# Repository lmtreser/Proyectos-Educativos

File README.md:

# Proyectos Educativos

Proyectos educativos (de diversos origenes) relacionados con trabajos prácticos de las escuelas EEST N°2, EEST N°3 y EEST N°5 de la ciudad de Mar del Plata.

Los diagramas esquemáticos en su mayoría están realizados con Autodesk EAGLE (v7 o superior), y en algunos casos con KiCad (v7 o superior). Mientras que el código generalmente está basado en la API de Arduino.

La ultima versión se puede descargar desde el repositorio [en este enlace](https://github.com/lmtreser/Proyectos).

## Contenidos

- `Analogicas 44` Trabajos "Aplicaciones de Electrónica Analógica I"
- `ArduProfe` Placa entrenadora para Arduino Nano, por el prof. Alejandro Cordero
- `Difusión` Charlas, eventos y difusiones en general
- `Diseño Asistido` Trabajos de diseño de esquemas y PCBs
- `Eduqube` PocketQube educative kit, by [Innova Space](https://www.innova-space.com)
- `Entrenadora Digital` Trabajo práctico "Aplicaciones de Electrónica Digital III"
- `Internet of Things` Trabajos relacionados al IoT
- `Lenguajes Electrónicos` Trabajos "Lenguajes Electrónicos II"
- `Micro Automata` Trabajo práctico "Montaje de Proyectos Electrónicos III"
- `Pulsador de Potencia` Feria de Ciencias, trabajo interdisciplinar, extracurricular
- `Robotec` Competencia de Robótica intercolegial, trabajo interdisciplinar, extracurricular
- `Sensor de Proximidad` Trabajo práctico "Montaje de Proyectos Electrónicos III"

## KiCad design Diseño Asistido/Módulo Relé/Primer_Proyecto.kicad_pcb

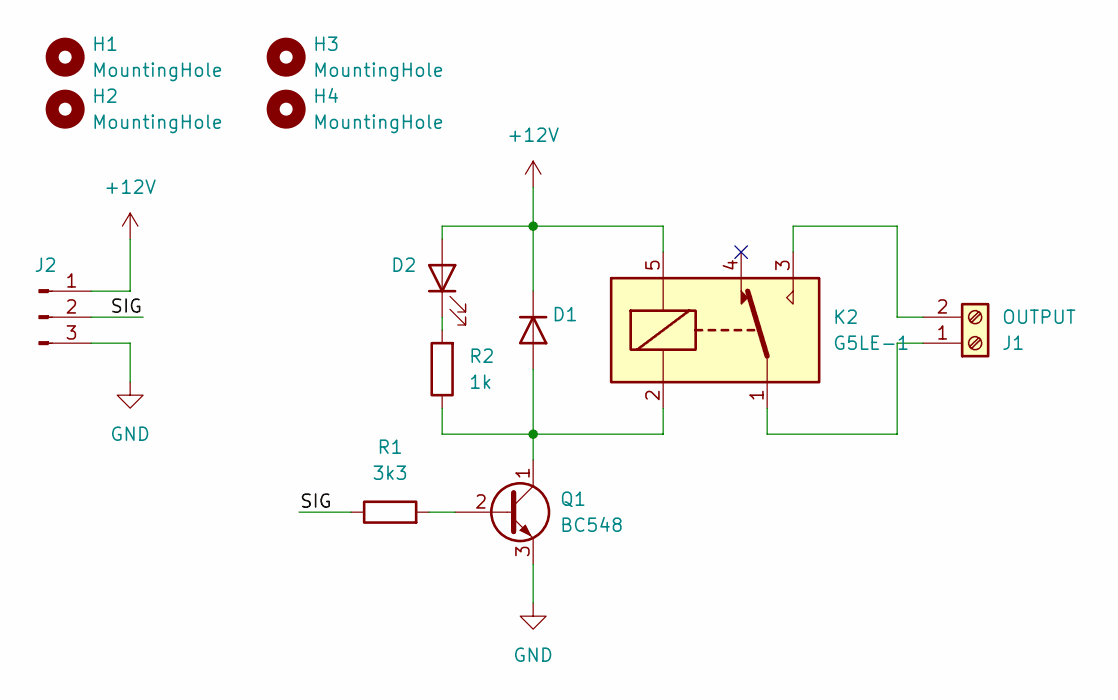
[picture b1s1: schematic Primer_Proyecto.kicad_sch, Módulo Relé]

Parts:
D1: 1N4007; D_DO-41_SOD81_P10.16mm_Horizontal
D2: LED; LED_D3.0mm
H1, H2, H3, H4: MountingHole; MountingHole_3.2mm_M3
J1: OUTPUT; TerminalBlock_MetzConnect_Type011_RT05502HBWC_1x02_P5.00mm_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
J2: Conn_01x03_Pin; PinHeader_1x03_P1.27mm_Vertical
K2: G5LE-1; Relay_SPDT_Omron-G5LE-1
Q1: BC548; TO-92_Inline
R1: 3k3; R_Axial_DIN0207_L6.3mm_D2.5mm_P7.62mm_Horizontal
R2: 1k; R_Axial_DIN0207_L6.3mm_D2.5mm_P7.62mm_Horizontal

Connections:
+12V: D1.1 (K), D2.2 (A), J2.1, K2.5
/SIG: J2.2, R1.1
GND: J2.3, Q1.3 (E)
unnamed: D1.2 (A), K2.2, Q1.1 (C), R2.1
unnamed: D2.1 (K), R2.2
unnamed: J1.1, K2.1
unnamed: J1.2, K2.3
unnamed: Q1.2 (B), R1.2

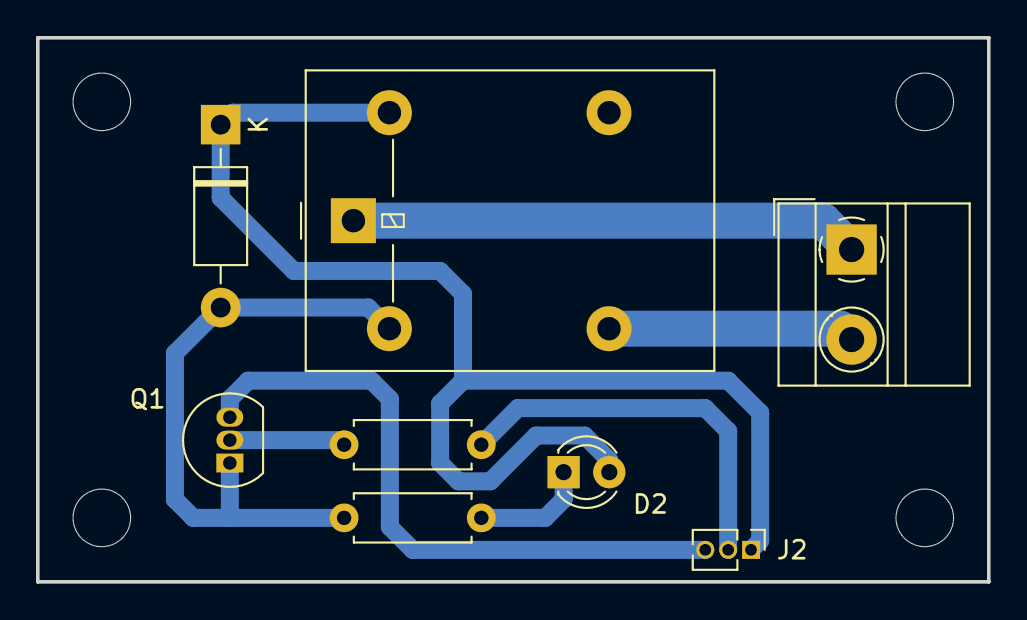
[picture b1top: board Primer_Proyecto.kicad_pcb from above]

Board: 2 copper layers, 52.8 x 30.2 mm, 12 parts (0 on the bottom side), 8 nets.

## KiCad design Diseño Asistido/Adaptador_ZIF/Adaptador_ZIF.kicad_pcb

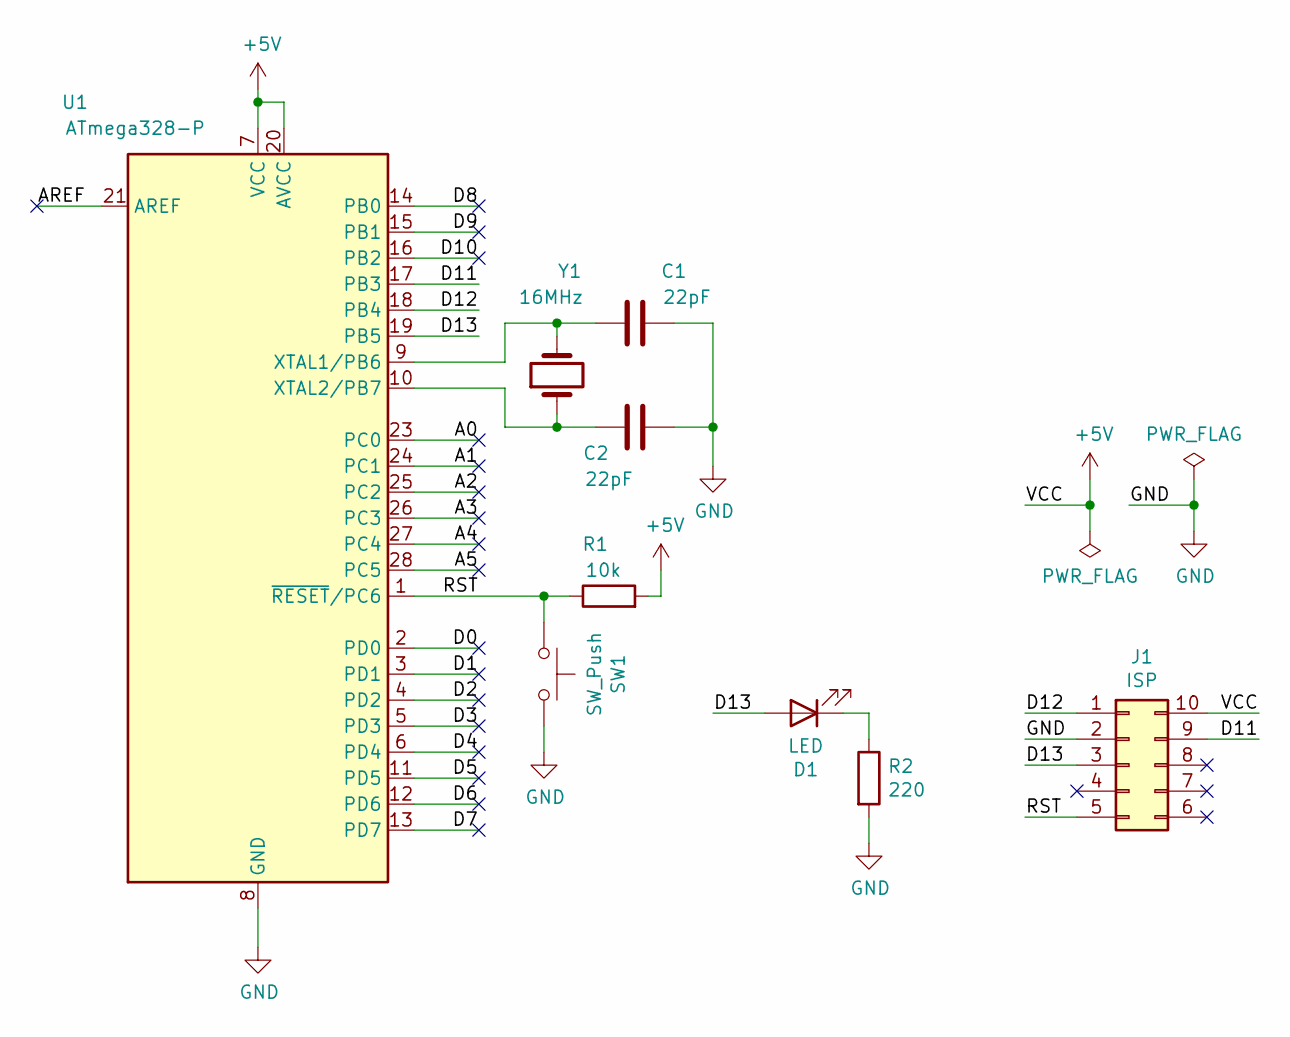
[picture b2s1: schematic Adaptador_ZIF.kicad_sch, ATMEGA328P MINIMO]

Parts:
C1, C2: 22pF; C_Disc_D5.0mm_W2.5mm_P2.50mm
D1: LED; LED_D3.0mm
J1: ISP; IDC-Header_2x05_P2.54mm_Vertical
R1: 10k; R_Axial_DIN0207_L6.3mm_D2.5mm_P10.16mm_Horizontal
R2: 220; R_Axial_DIN0207_L6.3mm_D2.5mm_P10.16mm_Horizontal
SW1: SW_Push; SW_PUSH_6mm_H5mm
U1: ATmega328-P; DIP_Socket-28_W6.9_W7.62_W10.16_W12.7_W13.5_3M_228-4817-00-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
Y1: 16MHz; Crystal_HC49-4H_Vertical

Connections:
+5V: J1.10, R1.2, U1.7 (VCC), U1.20 (AVCC)
/A0: U1.23 (PC0)
/A1: U1.24 (PC1)
/A2: U1.25 (PC2)
/A3: U1.26 (PC3)
/A4: U1.27 (PC4)
/A5: U1.28 (PC5)
/AREF: U1.21 (AREF)
/D0: U1.2 (PD0)
/D1: U1.3 (PD1)
/D2: U1.4 (PD2)
/D3: U1.5 (PD3)
/D4: U1.6 (PD4)
/D5: U1.11 (PD5)
/D6: U1.12 (PD6)
/D7: U1.13 (PD7)
/D8: U1.14 (PB0)
/D9: U1.15 (PB1)
/D10: U1.16 (PB2)
/D11: J1.9, U1.17 (PB3)
/D12: J1.1, U1.18 (PB4)
/D13: D1.2 (A), J1.3, U1.19 (PB5)
/RST: J1.5, R1.1, SW1.1, U1.1 (~RESET/PC6)
GND: C1.1, C2.1, J1.2, R2.2, SW1.2, U1.8 (GND), U1.22 (GND)
unnamed: C1.2, U1.9 (XTAL1/PB6), Y1.2
unnamed: C2.2, U1.10 (XTAL2/PB7), Y1.1
unnamed: D1.1 (K), R2.1

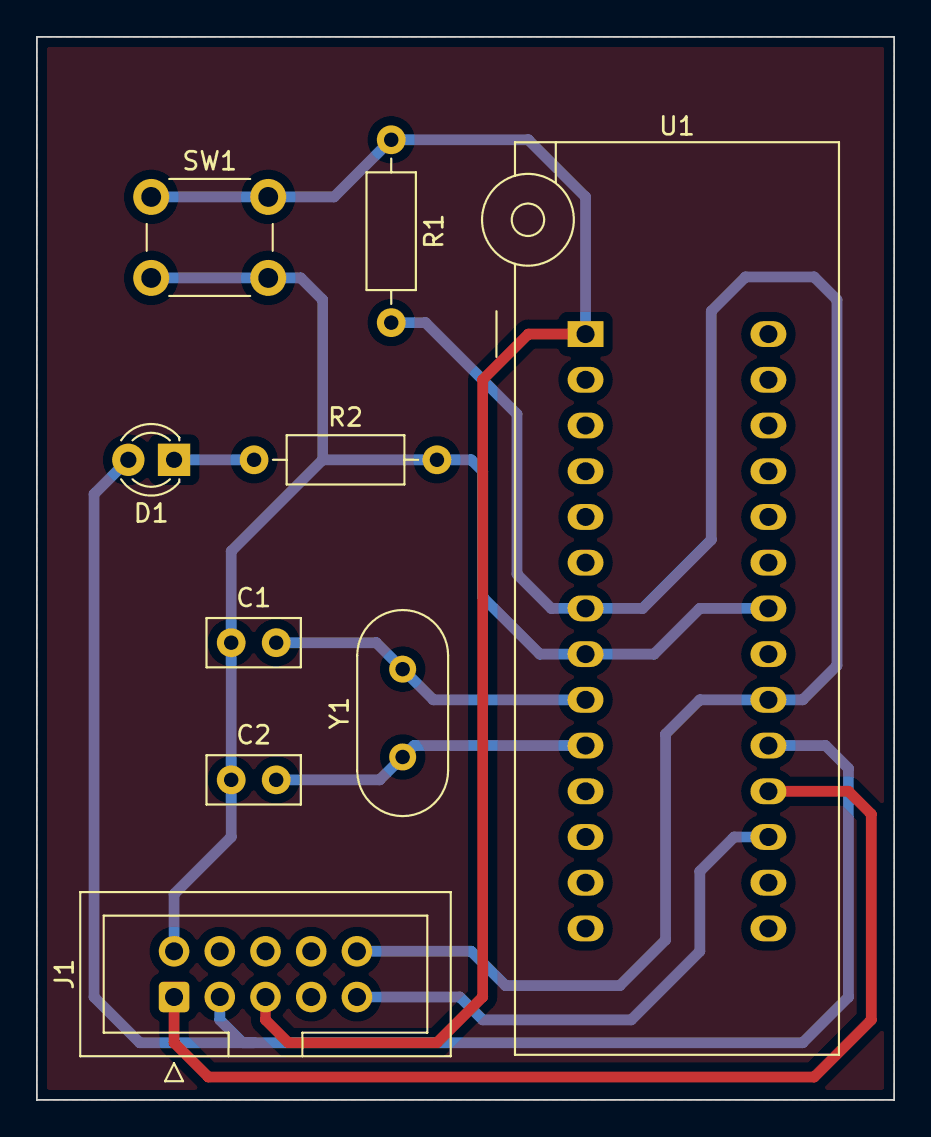
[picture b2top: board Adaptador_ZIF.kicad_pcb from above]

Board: 2 copper layers, 47.6 x 59.1 mm, 9 parts (0 on the bottom side), 9 nets.

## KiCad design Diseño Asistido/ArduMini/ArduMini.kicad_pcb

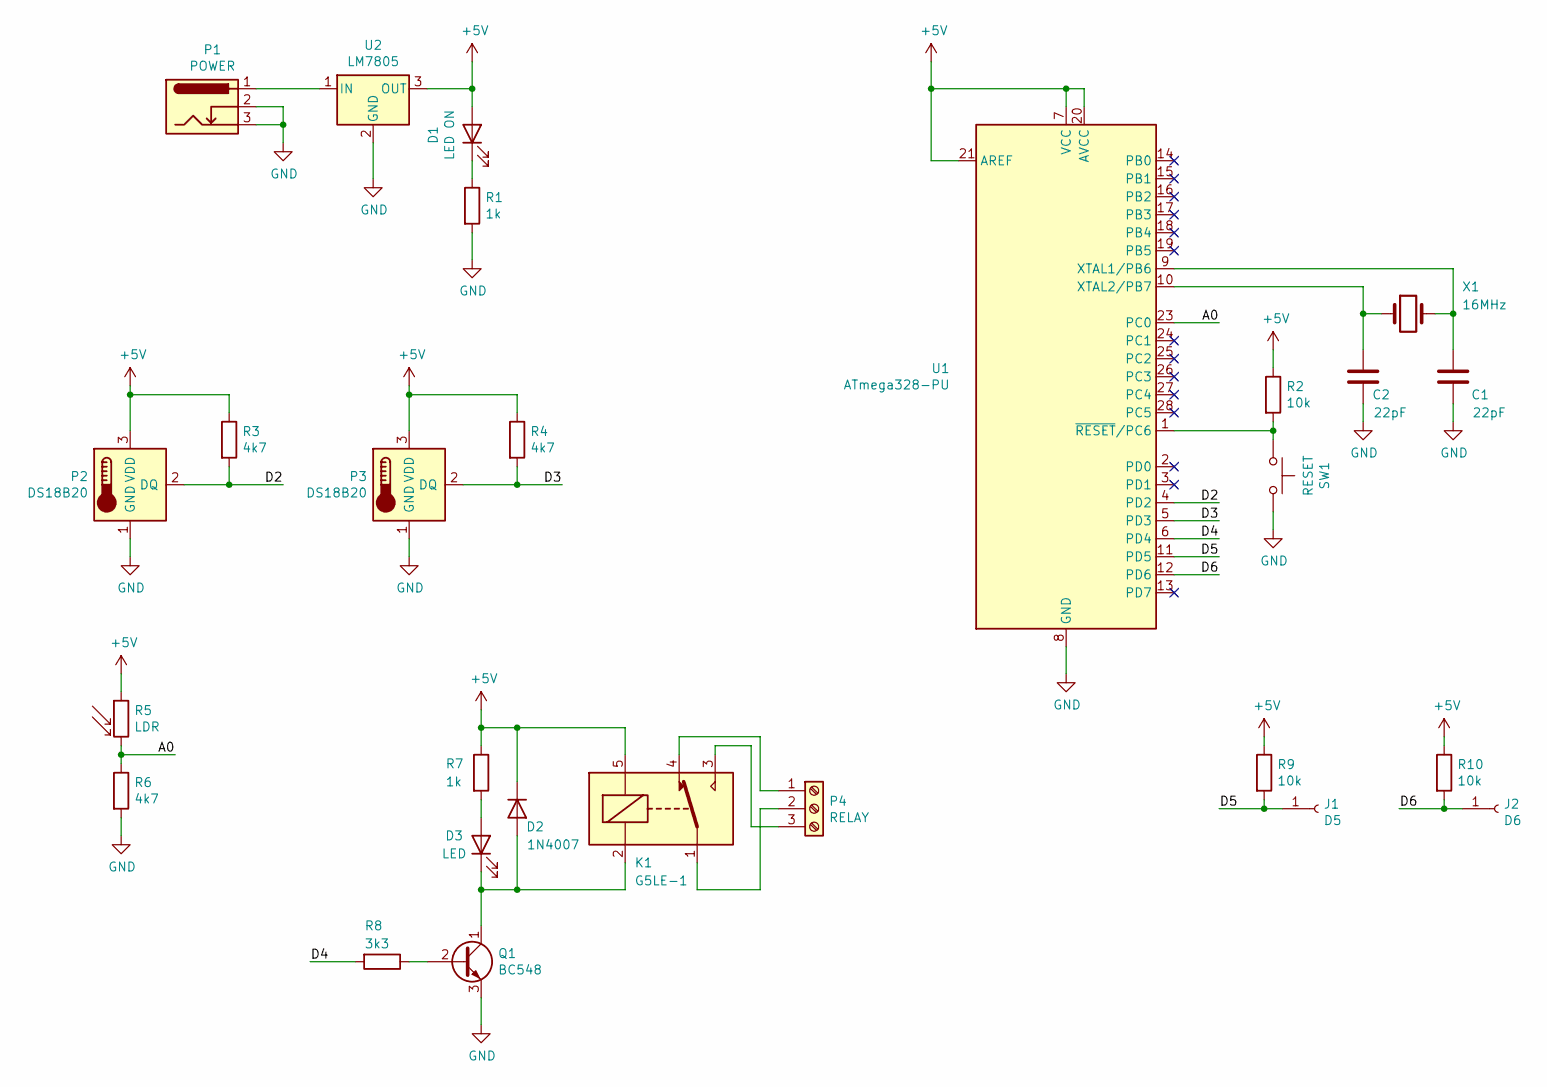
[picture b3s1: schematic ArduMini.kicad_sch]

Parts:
C1, C2: 22pF; C_Disc_D5.0mm_W2.5mm_P2.50mm
D1: LED ON; LED_D5.0mm
D2: 1N4007; D_DO-41_SOD81_P10.16mm_Horizontal
D3: LED; LED_D3.0mm
J1: D5; PinHeader_1x01_P1.00mm_Vertical
J2: D6; PinHeader_1x01_P1.00mm_Vertical
K1: G5LE-1; Relay_SPDT_Omron-G5LE-1
P1: POWER; BarrelJack_Horizontal
P2, P3: DS18B20; TerminalBlock_Altech_AK300-3_P5.00mm
P4: RELAY; TerminalBlock_Altech_AK300-3_P5.00mm
Q1: BC548; TO-92_Inline
R1, R7: 1k; R_Axial_DIN0207_L6.3mm_D2.5mm_P10.16mm_Horizontal
R2, R9, R10: 10k; R_Axial_DIN0207_L6.3mm_D2.5mm_P10.16mm_Horizontal
R3, R4, R6: 4k7; R_Axial_DIN0207_L6.3mm_D2.5mm_P10.16mm_Horizontal
R5: LDR; R_LDR_5.0x4.1mm_P3mm_Vertical
R8: 3k3; R_Axial_DIN0207_L6.3mm_D2.5mm_P10.16mm_Horizontal
SW1: RESET; SW_PUSH_6mm_H5mm
U1: ATmega328-PU; DIP-28_W7.62mm
U2: LM7805; TO-220-3_Vertical
X1: 16MHz; Crystal_HC49-4H_Vertical

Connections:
+5V: D1.2 (A), D2.1 (K), K1.5, P2.3 (VDD), P3.3 (VDD), R2.1, R3.1, R4.1, R5.1, R7.1, R9.1, R10.1, U1.7 (VCC), U1.20 (AVCC), U1.21 (AREF), U2.3 (OUT)
/A0: R5.2, R6.1, U1.23 (PC0)
/D2: P2.2 (DQ), R3.2, U1.4 (PD2)
/D3: P3.2 (DQ), R4.2, U1.5 (PD3)
/D4: R8.2, U1.6 (PD4)
/D5: J1.1, R9.2, U1.11 (PD5)
/D6: J2.1, R10.2, U1.12 (PD6)
GND: C1.1, C2.1, P1.2, P1.3, P2.1 (GND), P3.1 (GND), Q1.3 (E), R1.2, R6.2, SW1.2, U1.8 (GND), U1.22 (GND), U2.2 (GND)
unnamed: C1.2, U1.9 (XTAL1/PB6), X1.2
unnamed: C2.2, U1.10 (XTAL2/PB7), X1.1
unnamed: D1.1 (K), R1.1
unnamed: D2.2 (A), D3.1 (K), K1.2, Q1.1 (C)
unnamed: D3.2 (A), R7.2
unnamed: K1.1, P4.2
unnamed: K1.3, P4.3
unnamed: K1.4, P4.1
unnamed: P1.1, U2.1 (IN)
unnamed: Q1.2 (B), R8.1
unnamed: R2.2, SW1.1, U1.1 (~RESET/PC6)

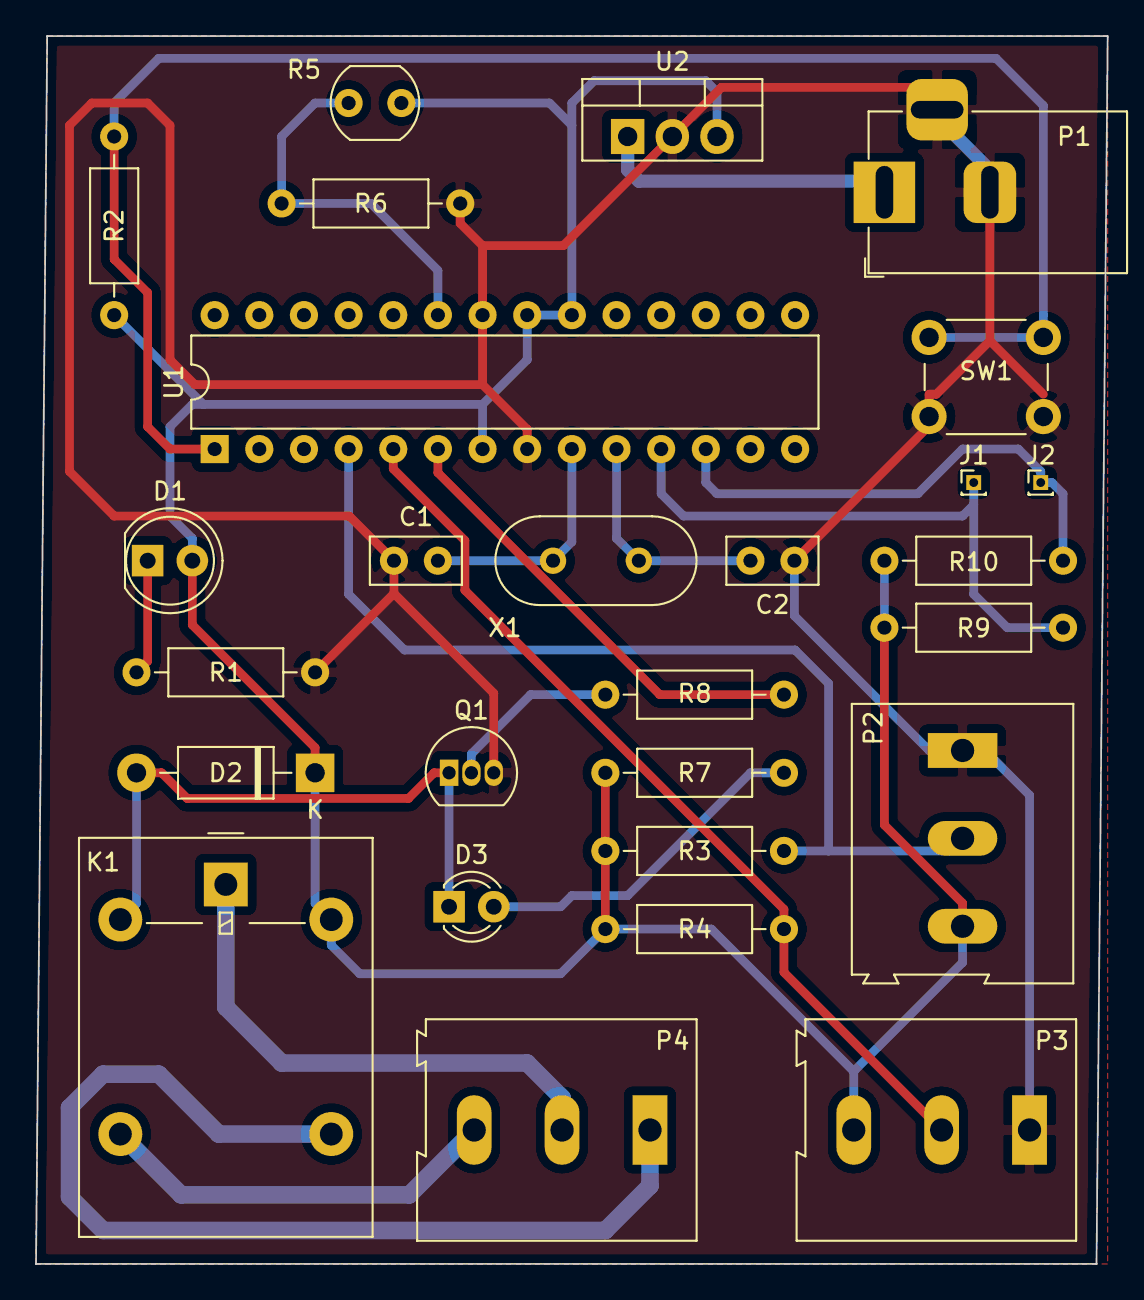
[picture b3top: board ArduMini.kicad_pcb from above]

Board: 2 copper layers, 61.0 x 69.9 mm, 27 parts (0 on the bottom side), 19 nets.

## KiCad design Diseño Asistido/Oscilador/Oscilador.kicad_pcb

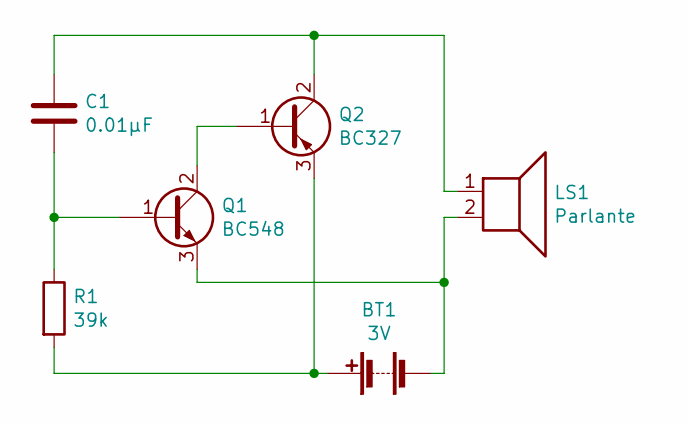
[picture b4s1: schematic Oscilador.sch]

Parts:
BT1: 3V; BatteryHolder_Keystone_2462_2xAA
C1: 0.01µF; C_Disc_D5.0mm_W2.5mm_P2.50mm
LS1: Parlante; TerminalBlock_Altech_AK300-2_P5.00mm
Q1: BC548; TO-92
Q2: BC327; TO-92
R1: 39k; R_Axial_DIN0207_L6.3mm_D2.5mm_P15.24mm_Horizontal

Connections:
unnamed: BT1.1 (+), Q2.3 (E), R1.2
unnamed: BT1.2 (-), LS1.2, Q1.3 (E)
unnamed: C1.1, LS1.1, Q2.2 (C)
unnamed: C1.2, Q1.1 (B), R1.1
unnamed: Q1.2 (C), Q2.1 (B)

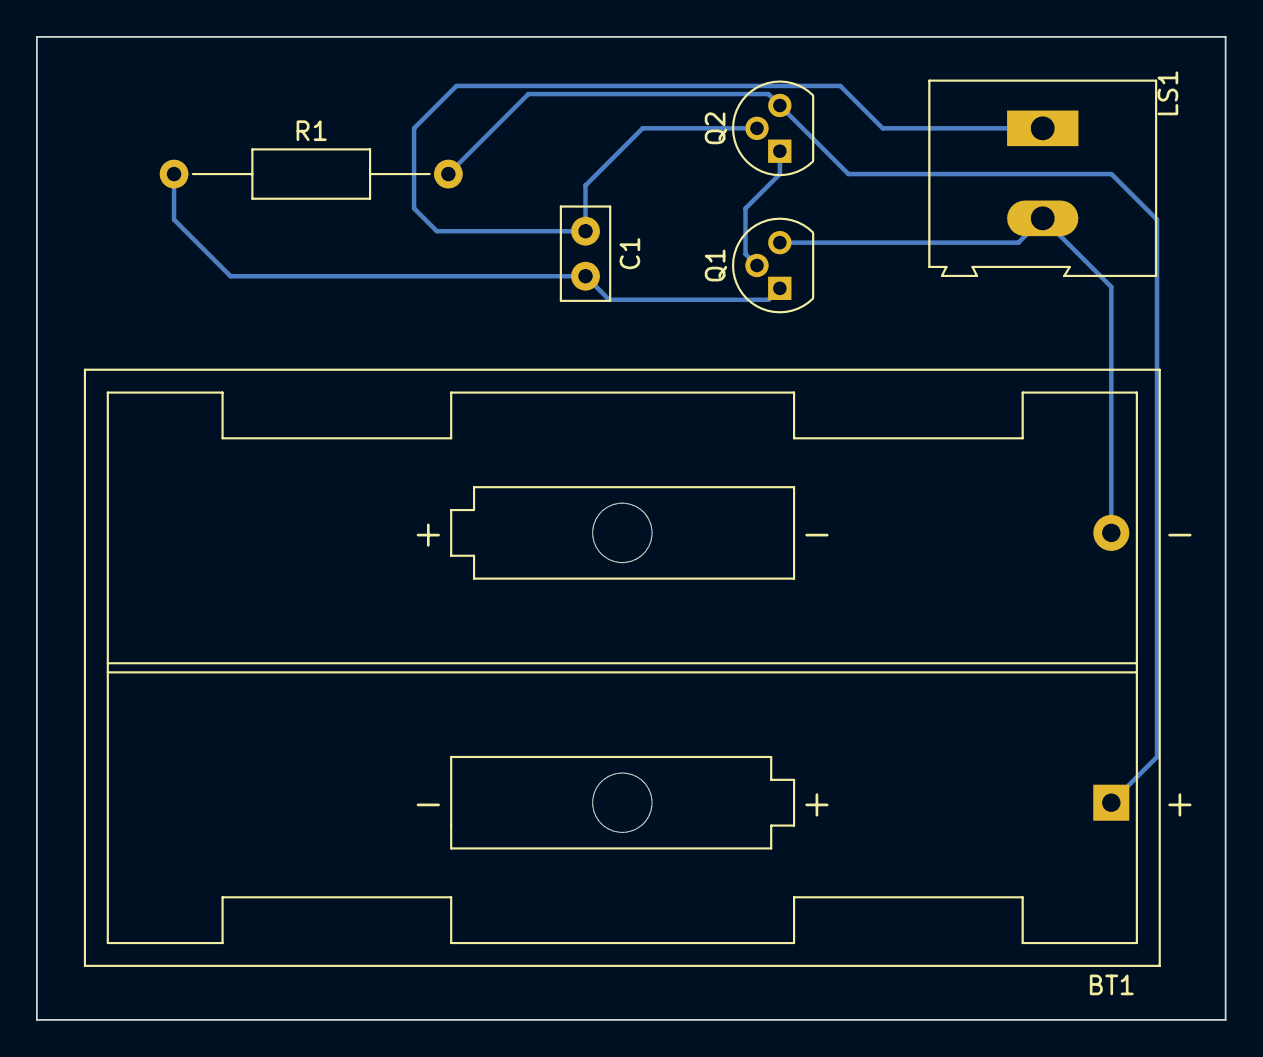
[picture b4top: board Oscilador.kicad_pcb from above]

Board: 2 copper layers, 66.0 x 54.6 mm, 6 parts (0 on the bottom side), 5 nets.

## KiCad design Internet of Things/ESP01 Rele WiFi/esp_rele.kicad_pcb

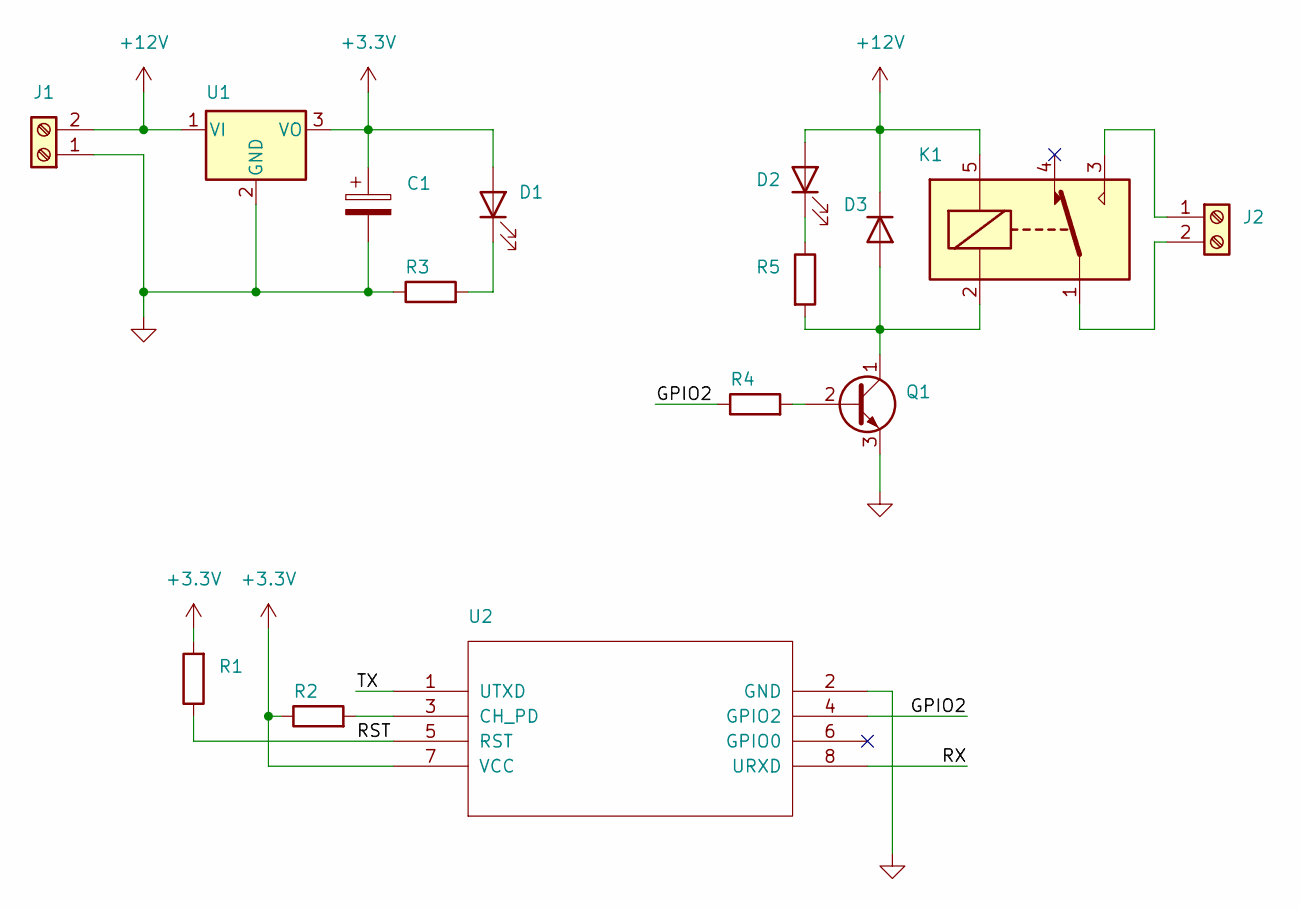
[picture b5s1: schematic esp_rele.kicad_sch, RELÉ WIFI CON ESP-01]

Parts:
C1: 25uF; CP_Radial_D6.3mm_P2.50mm
D1, D2: LED; LED_D3.0mm
D3: 1N4007; D_DO-41_SOD81_P10.16mm_Horizontal
J1, J2: Screw_Terminal_01x02; TerminalBlock_Phoenix_MKDS-1,5-2_1x02_P5.00mm_Horizontal
K1: G5LE-1; Relay_SPDT_Omron-G5LE-1
Q1: BC548; TO-92_Inline
R1, R2, R4: 3k3; R_Axial_DIN0207_L6.3mm_D2.5mm_P7.62mm_Horizontal
R3, R5: 470; R_Axial_DIN0207_L6.3mm_D2.5mm_P7.62mm_Horizontal
U1: AZ1117T; TO-220-3_Vertical
U2: ESP-01v090; ESP-01

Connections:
+3.3V: C1.1, D1.2 (A), R1.2, R2.1, U1.3 (VO), U2.7 (VCC)
+12V: D2.2 (A), D3.1 (K), J1.2, K1.5, U1.1 (VI)
/GPIO2: R4.1, U2.4 (GPIO2)
/RST: R1.1, U2.5 (RST)
/RX: U2.8 (URXD)
/TX: U2.1 (UTXD)
GND: C1.2, J1.1, Q1.3 (E), R3.1, U1.2 (GND), U2.2 (GND)
unnamed: D1.1 (K), R3.2
unnamed: D2.1 (K), R5.1
unnamed: D3.2 (A), K1.2, Q1.1 (C), R5.2
unnamed: J2.1, K1.3
unnamed: J2.2, K1.1
unnamed: Q1.2 (B), R4.2
unnamed: R2.2, U2.3 (CH_PD)

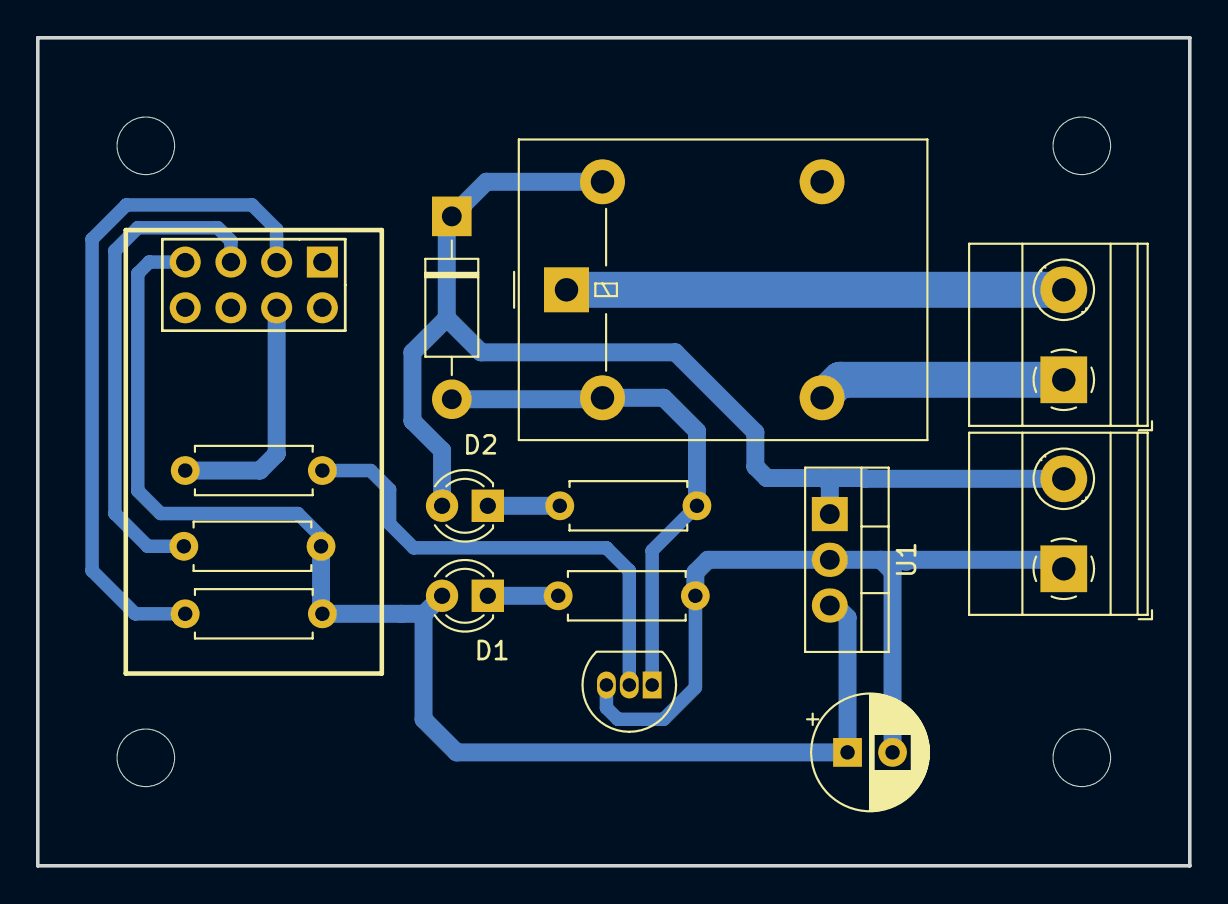
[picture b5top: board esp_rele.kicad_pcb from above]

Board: 2 copper layers, 64.0 x 46.0 mm, 19 parts (0 on the bottom side), 12 nets.

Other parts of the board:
REF01, REF02, REF03, REF04: MountingHole_3.2mm_M3

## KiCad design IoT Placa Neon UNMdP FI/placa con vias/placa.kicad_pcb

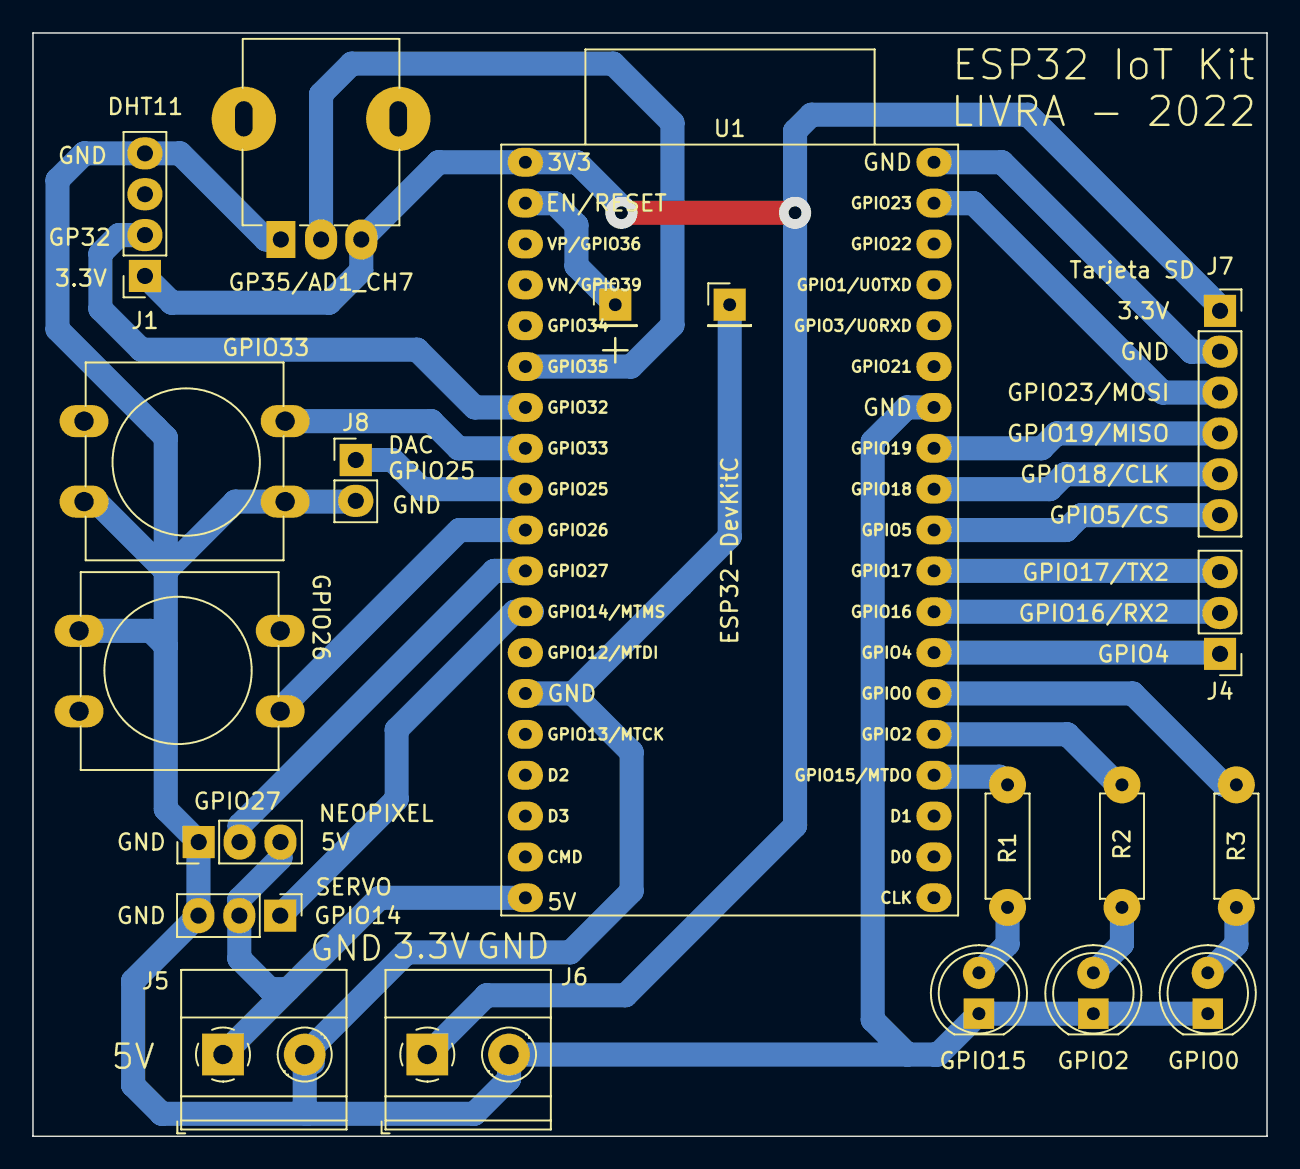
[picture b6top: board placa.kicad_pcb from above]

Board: 2 copper layers, 76.7 x 68.6 mm, 20 parts (0 on the bottom side), 24 nets.

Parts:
D1: ROJO; LED_D5.0mm
D2: AMARILLO; LED_D5.0mm
D3: VERDE; LED_D5.0mm
J1: DHT11; PinSocket_1x04_P2.54mm_Vertical
J2: NeoPixel; PinHeader_1x03_P2.54mm_Vertical
J3: Servo; PinHeader_1x03_P2.54mm_Vertical
J4: Conn_01x03_Male; PinHeader_1x03_P2.54mm_Vertical
J5, J6: Screw_Terminal_01x02; TerminalBlock_Phoenix_MKDS-1,5-2-5.08_1x02_P5.08mm_Horizont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
J7: Conn_01x06_Female; PinSocket_1x06_P2.54mm_Vertical
J8: Conn_01x02_Male; PinHeader_1x02_P2.54mm_Vertical
J11, J12: Conn_01x01_Male; PinHeader_1x01_P2.54mm_Vertical
R1, R2, R3: 470; R_Axial_DIN0207_L6.3mm_D2.5mm_P7.62mm_Horizontal
RV1: R_Potentiometer; Potentiometer_Alpha_RD901F-40-00D_Single_Vertical
SW1, SW2: SW_Push; SW_PUSH-12mm
U1: ESP32-DevKitC

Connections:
3.3v: J1.1, J6.1, J7.1, RV1.3, U1.1 (3V3)
5v: J2.3, J3.2, J5.1, U1.19 (5V)
/EN: J11.1, U1.2 (CHIP_PU)
GND: D1.1 (K), D2.1 (K), D3.1 (K), J1.4, J2.1, J3.3, J5.2, J6.2, J7.2, J8.2, J12.1, RV1.1, SW1.2, SW2.2, U1.14 (GND), U1.32 (GND), U1.38 (GND)
unnamed: D1.2 (A), R3.2
unnamed: D2.2 (A), R2.1
unnamed: D3.2 (A), R1.1
unnamed: J1.2, U1.7 (32K_XP/GPIO32/ADC1_CH4)
unnamed: J2.2, U1.11 (ADC2_CH7/GPIO27)
unnamed: J3.1, U1.12 (MTMS/GPIO14/ADC2_CH6)
unnamed: J4.1, U1.26 (ADC2_CH0/GPIO4)
unnamed: J4.2, U1.27 (GPIO16)
unnamed: J4.3, U1.28 (GPIO17)
unnamed: J7.3, U1.37 (GPIO23)
unnamed: J7.4, U1.31 (GPIO19)
unnamed: J7.5, U1.30 (GPIO18)
unnamed: J7.6, U1.29 (*GPIO5)
unnamed: R1.2, U1.23 (*MTDO/GPIO15/ADC2_CH3)
unnamed: R2.2, U1.24 (ADC2_CH2/*GPIO2)
unnamed: R3.1, U1.25 (*GPIO0/BOOT/ADC2_CH1)
unnamed: RV1.2, U1.6 (VDET_2/GPIO35/ADC1_CH7)
btn1: SW1.1, U1.8 (32K_XN/GPIO33/ADC1_CH5)
btn2: SW2.1, U1.10 (DAC_2/ADC2_CH9/GPIO26)
dac: J8.1, U1.9 (DAC_1/ADC2_CH8/GPIO25)

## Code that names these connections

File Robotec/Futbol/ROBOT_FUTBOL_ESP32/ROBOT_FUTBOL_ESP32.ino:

/*
  ROBOT_FUTBOL - Control por Bluetooth con ESP32
  ------------------------------------------------
  Placa: ESP32 NodeMCU WROOM 38 pines
  Driver de motores: L298N
  App recomendada: "Bluetooth RC Controller"

  Comandos por Bluetooth:
    F/B/L/R/S = adelante/atrás/izq/der/stop
    G/I/H/J   = diagonales (adel-izq, adel-der, atrás-izq, atrás-der)
    0-9, q    = velocidad (PWM 80-180)
*/

#include "BluetoothSerial.h"

#if !defined(CONFIG_BT_ENABLED) || !defined(CONFIG_BLUEDROID_ENABLED)
#error Bluetooth no está habilitado. Verifica la configuración de la placa.
#endif

BluetoothSerial SerialBT;

// --- Pines del L298N (lado derecho físico del ESP32) ---
int VelocidadMotor1 = 17; // GPIO17 -> ENA (PWM motor A)   | pata física N°28
int VelocidadMotor2 = 16; // GPIO16 -> ENB (PWM motor B)   | pata física N°27
int Motor1A = 4;          // GPIO4  -> IN1 (dirección A)   | pata física N°26
int Motor1B = 2;          // GPIO2  -> IN2 (dirección A)   | pata física N°24
int Motor2C = 15;         // GPIO15 -> IN3 (dirección B)   | pata física N°23
int Motor2D = 5;          // GPIO5  -> IN4 (dirección B)   | pata física N°29

// --- Configuración PWM (API nueva del core ESP32 3.x) ---
const int frecuenciaPWM = 5000;
const int resolucionPWM = 8;

int speedMotor = 150; // velocidad por defecto (rango 80-180)
char comando;

void setup() {
  Serial.begin(115200);
  SerialBT.begin("ROBOT_FUTBOL");
  Serial.println("ROBOT_FUTBOL listo. Esperando conexión Bluetooth...");

  pinMode(Motor1A, OUTPUT);
  pinMode(Motor1B, OUTPUT);
  pinMode(Motor2C, OUTPUT);
  pinMode(Motor2D, OUTPUT);

  ledcAttach(VelocidadMotor1, frecuenciaPWM, resolucionPWM);
  ledcAttach(VelocidadMotor2, frecuenciaPWM, resolucionPWM);

  detenerMotores();
}

void loop() {
  if (SerialBT.available()) {
    comando = SerialBT.read();
    Serial.print("Comando recibido: ");
    Serial.println(comando);
    ejecutarComando(comando);
  }
}

void ejecutarComando(char cmd) {
  switch (cmd) {
    case 'F': moveForward(); break;
    case 'B': moveBackward(); break;
    case 'L': turnLeft(); break;
    case 'R': turnRight(); break;
    case 'S': detenerMotores(); break;
    case 'G': moveForwardLeft(); break;
    case 'I': moveForwardRight(); break;
    case 'H': moveBackwardsLeft(); break;
    case 'J': moveBackwardsRight(); break;
    case 'q':
      speedMotor = 180;
      actualizarVelocidad();
      break;
    default:
      if (cmd >= '0' && cmd <= '9') {
        int nivel = cmd - '0';
        speedMotor = map(nivel, 0, 9, 80, 180);
        actualizarVelocidad();
      }
      break;
  }
}

void actualizarVelocidad() {
  ledcWrite(VelocidadMotor1, speedMotor);
  ledcWrite(VelocidadMotor2, speedMotor);
}

// --- Movimientos básicos ---

void moveForward() {
  digitalWrite(Motor1A, HIGH);
  digitalWrite(Motor1B, LOW);
  digitalWrite(Motor2C, HIGH);
  digitalWrite(Motor2D, LOW);
  actualizarVelocidad();
}

void moveBackward() {
  digitalWrite(Motor1A, LOW);
  digitalWrite(Motor1B, HIGH);
  digitalWrite(Motor2C, LOW);
  digitalWrite(Motor2D, HIGH);
  actualizarVelocidad();
}

void turnLeft() {
  digitalWrite(Motor1A, LOW);
  digitalWrite(Motor1B, HIGH);
  digitalWrite(Motor2C, HIGH);
  digitalWrite(Motor2D, LOW);
  actualizarVelocidad();
}

void turnRight() {
  digitalWrite(Motor1A, HIGH);
  digitalWrite(Motor1B, LOW);
  digitalWrite(Motor2C, LOW);
  digitalWrite(Motor2D, HIGH);
  actualizarVelocidad();
}

void detenerMotores() {
  digitalWrite(Motor1A, LOW);
  digitalWrite(Motor1B, LOW);
  digitalWrite(Motor2C, LOW);
  digitalWrite(Motor2D, LOW);
  ledcWrite(VelocidadMotor1, 0);
  ledcWrite(VelocidadMotor2, 0);
}

// --- Diagonales (motor "de adentro" a velocidad reducida, no detenido) ---

void moveForwardLeft() {
  int velExtra = min(speedMotor + 30, 180);
  digitalWrite(Motor1A, HIGH);
  digitalWrite(Motor1B, LOW);
  digitalWrite(Motor2C, HIGH);
  digitalWrite(Motor2D, LOW);
  ledcWrite(VelocidadMotor1, speedMotor - 40 < 0 ? 0 : speedMotor - 40); // motor izquierdo más lento
  ledcWrite(VelocidadMotor2, velExtra);
}

void moveForwardRight() {
  int velExtra = min(speedMotor + 30, 180);
  digitalWrite(Motor1A, HIGH);
  digitalWrite(Motor1B, LOW);
  digitalWrite(Motor2C, HIGH);
  digitalWrite(Motor2D, LOW);
  ledcWrite(VelocidadMotor1, velExtra);
  ledcWrite(VelocidadMotor2, speedMotor - 40 < 0 ? 0 : speedMotor - 40); // motor derecho más lento
}

void moveBackwardsLeft() {
  int velExtra = min(speedMotor + 30, 180);
  digitalWrite(Motor1A, LOW);
  digitalWrite(Motor1B, HIGH);
  digitalWrite(Motor2C, LOW);
  digitalWrite(Motor2D, HIGH);
  ledcWrite(VelocidadMotor1, speedMotor - 40 < 0 ? 0 : speedMotor - 40);
  ledcWrite(VelocidadMotor2, velExtra);
}

void moveBackwardsRight() {
  int velExtra = min(speedMotor + 30, 180);
  digitalWrite(Motor1A, LOW);
  digitalWrite(Motor1B, HIGH);
  digitalWrite(Motor2C, LOW);
  digitalWrite(Motor2D, HIGH);
  ledcWrite(VelocidadMotor1, velExtra);
  ledcWrite(VelocidadMotor2, speedMotor - 40 < 0 ? 0 : speedMotor - 40);
}

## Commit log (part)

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2023-12-02 Micro Automata con Arduino
2023-12-02 Actualizado README
2023-12-02 Sensor de proximidad IR
2023-12-02 Robotec Sigue-Lineas EEST N°3
2023-12-02 Competencia de Robótica
2023-12-02 Firmware Arduino para test de hardware
2023-12-02 Placa Mubi-Bot / Prof. Oyarburo
2023-12-02 Eliminado de archivos innecesarios
2023-12-02 Sigue-Lineas E.E.S.T. N°3
2023-12-02 Vúmetro con Arduino
2023-12-02 Firmware para pruebas
2023-12-02 Placa de desarrollo ESP32 Neon UNMdP FI
2023-12-02 Relé WiFi con ESP-01
2023-12-02 Pulsador de Potencia E.E.E. N°513
2023-12-02 Entrenadora Digital
2023-12-02 Amplificador 8W con TDA2003
2023-12-02 Internet de las cosas
2023-12-02 Robot Sigue-Lineas Ciclo Básico
2023-12-02 Amplificador 8W EEST N°2
2023-12-02 Vumetro con Arduino EEST N°2
2023-12-02 Actualización de archivos
2023-12-02 Diagrama esquemático
2023-12-04 Entrenadora Digital con Arduino
2023-12-04 Pulsador de Potencia
2023-12-06 Lista de materiales
2023-12-08 STL gabinete
2023-12-28 Actualización readme
2023-12-28 Documentación
2023-12-28 Reglamento Sumo v2022
2023-12-28 Reglamento Carreras v2022
2023-12-28 Reglamento Laberintos v2022
2023-12-28 Sugerencias JL Bruni
2024-02-01 update docs
2024-02-01 add src js Clicker
2024-02-03 update Project Neon UNMdP FI
2024-02-06 Actualizar README.md
2024-02-06 add dase
2024-02-21 Amplificador de auriculares
2024-02-21 Entrenadora PICAXE-08
2024-02-21 Control de velocidad para motor DC
2024-02-21 Acondicionador para caudalimetro
2024-02-21 Divisor de frecuencia
2024-02-21 Sistema con PICmicro para máquina Vortex
2024-02-21 PedalPhone
2024-02-21 Datalogger
2024-02-21 ArduiMini
2024-02-21 Adaptador ZIF
2024-02-21 Coron DS7 Clone
2024-03-05 add charla perfil de un tecnico
2024-03-07 add ArduProfe
2024-03-07 add Innova Space Eduqube
2024-03-12 update entrenadora digital
2024-03-18 add Sensor de temperatura
2024-03-26 update MUBI-BOT
2024-05-07 add modulo rele
2024-05-07 update sensor temperatura
2024-05-16 add datalogger
2024-05-16 add wokwi files
2024-05-16 add arduino sketch
2024-05-16 add arduino binaries
2024-05-16 add simulacion (SimulIDE-1.0.0-SR2 R1449)
2024-05-17 add Vení a la Técnica
2024-06-05 update datalogger
2024-07-31 update sch & brd
2024-08-09 update dirs
2024-08-09 add motor pap driver
2024-08-16 add dispositivo domotico
2024-08-16 add ino file
2024-09-06 add firmware modbus rtu
2024-09-13 add driver tester servos
2024-09-14 add 555 inventable
2024-09-19 add ntc table
2024-09-26 add esp32 wiring
2024-09-27 add mqtt example
2024-10-03 update modbusrtu
2024-10-07 update objects visibility
2024-10-07 add Eyes
2025-01-23 add Maze-Solving-Algorithms-Comparison
2025-02-14 add robot diferencial pdf
2025-03-25 add control motor DC
2025-03-25 add robot laberintos
2025-03-25 add algorithms
2025-04-01 modified chassis
2025-04-01 add fermin dase projects
2025-04-04 add algoritmo llenado
2025-04-22 update eagle project
2025-05-16 add Control Remoto
2025-05-16 fix buttons
2025-05-16 fix ui, buttons
2025-05-21 add analogico.html
2025-05-23 update html
2025-06-12 update htmls
2025-06-12 update analogico
2025-06-12 update gap
2025-06-30 add docs
2025-07-01 add micromouse robot
2025-07-05 add tabla comparativa
2025-07-09 update modulo rele
2025-07-10 add chassis labe v1
2025-07-10 update chassis
2025-07-15 update robot labe
2025-07-16 sch/pcb eagle fermin
2025-07-16 update 3d model
2025-07-16 mubi-bot3 v4, kicad project (legacy)
2025-07-16 update sch pcb kicad v9
2025-07-19 update sch & pcb
2025-07-19 add img 3d
2025-07-19 update sch&pcb&step
2025-07-19 rm old files
2025-07-19 update chassis 3d
2025-08-01 update project
2025-08-01 add backups
2025-08-01 update chassis+sensor
2025-08-01 add ultrasonic stl
2025-08-02 update chassis, ultrasonic
2025-08-06 add motor assembly right stl
2025-08-06 add main project
2025-08-06 update main
2025-08-07 add gitignore
2025-08-07 remove fcbak
2025-08-10 add ultrasonic sensor support
2025-08-11 add crazy support
2025-08-11 add chassis
2025-08-11 add wheel
2025-08-11 add motor assembly
2025-08-11 add reforma tracking
2025-08-11 update wheel design
2025-08-14 add steps ruedas
2025-08-14 update crazy support
2025-08-14 update wheel
2025-08-19 add joystick v2
2025-08-20 add p5.js demo
2025-08-27 add reglamentos 2025
2025-08-27 update reglamentos
2025-08-27 add poster 2025
2025-09-08 update wheel, finish work
2025-09-08 update assembly project
2025-09-09 update main file
2025-09-29 update robotec repo
2025-10-01 rm files
2025-10-01 paper pid carreras
2025-11-05 add modalidad fútbol robot
2025-11-05 add tecnobot kits
2025-11-05 add DuinoBot info
2025-11-05 add duinobot v2.4 arduino lib
2025-11-08 micro automata v1
2025-11-08 add v2: node-red
2025-11-08 add v2 firmware
2025-11-08 add schematics
2025-11-16 add petri network draft
2025-11-16 add fsm drafts
2026-02-18 add LM567 datasheet
2026-02-18 add ULN200x datasheet
